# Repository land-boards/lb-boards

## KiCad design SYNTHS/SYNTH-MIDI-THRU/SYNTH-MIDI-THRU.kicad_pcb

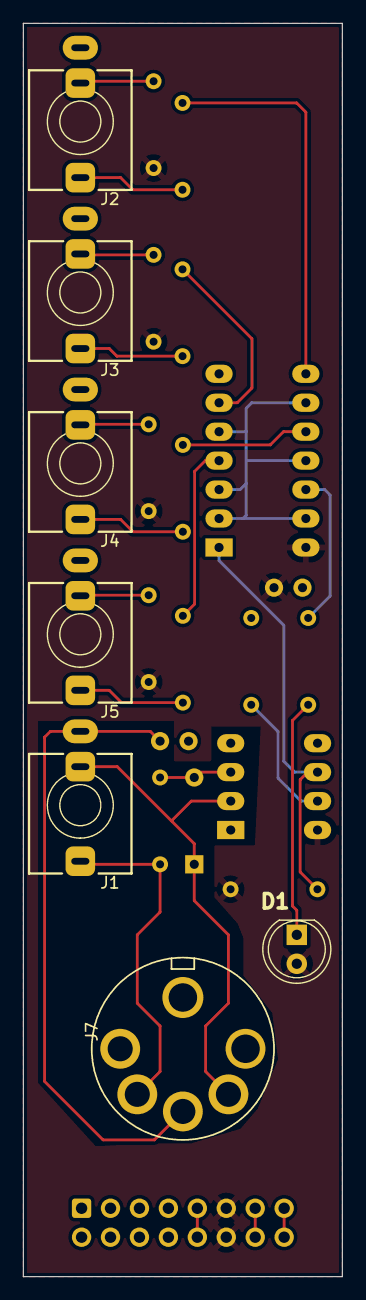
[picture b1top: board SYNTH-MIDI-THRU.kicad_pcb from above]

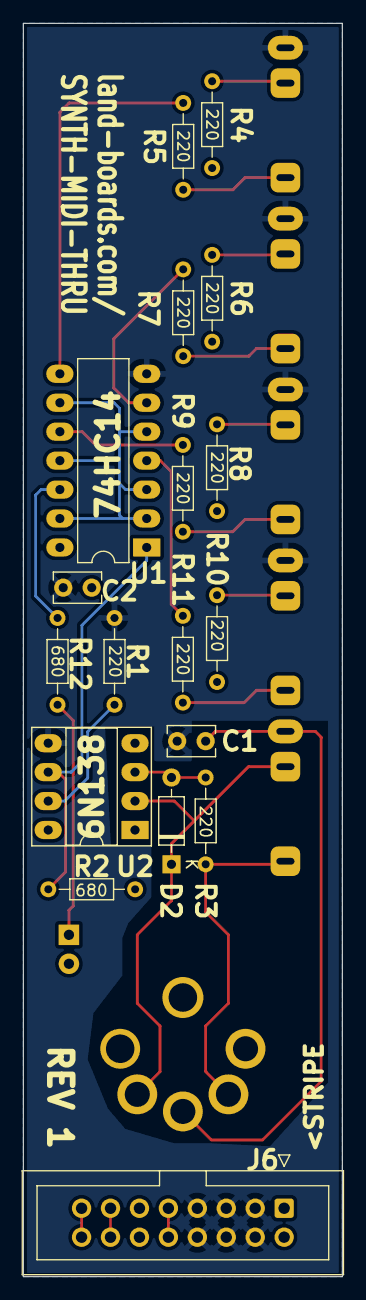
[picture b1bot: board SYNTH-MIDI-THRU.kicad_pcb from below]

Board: 2 copper layers, 28.0 x 110.0 mm, 25 parts (18 on the bottom side), 26 nets.

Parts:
C1, C2: 0.1uF; C_Rect_L4.0mm_W2.5mm_P2.50mm
D1: LED; LED_D5.0mm
D2: 1N914; D_DO-35_SOD27_P7.62mm_Horizontal
J1, J2, J3, J4, J5: AudioJack3; PJ-366ST
J6: Conn_02x08_Odd_Even; IDC-Header_2x08_P2.54mm_Vertical
J7: DIN-5; DIN-5_SD-50BV-Vertical
R1, R3, R4, R5, R6, R7, R8, R9, R10, R11: 220; R_Axial_DIN0204_L3.6mm_D1.6mm_P7.62mm_Horizontal
R2, R12: 680; R_Axial_DIN0204_L3.6mm_D1.6mm_P7.62mm_Horizontal
U1: 74HC14; DIP-14_W7.62mm_LongPads
U2: 6N138; DIP-8_W7.62mm_Socket_LongPads

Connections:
+5V: C2.1, D1.2 (A), J6.11, J6.12, R2.1, R4.1, R6.1, R8.1, R10.1, U1.14 (VCC), U2.8 (VCC)
+12V: J6.9, J6.10
/ALLRXD: U1.2, U1.3, U1.5, U1.9, U1.11, U1.13
/CV_OUT: J6.13, J6.14
/GATE_OUT: J6.15, J6.16
/MIDI_1_OUT: J2.T, R5.2
/MIDI_1_PWR: J2.R, R4.2
/MIDI_2_OUT: J3.T, R7.2
/MIDI_2_PWR: J3.R, R6.2
/MIDI_3_OUT: J4.T, R9.2
/MIDI_3_PWR: J4.R, R8.2
/MIDI_4_OUT: J5.T, R11.2
/MIDI_4_PWR: J5.R, R10.2
/MIDI_GND: C1.1, J1.S, J7.2
/MIDI_IN: D2.1 (K), J1.R, J7.4, U2.2 (C1)
/MIDI_RTN: J1.T, J7.5, R3.2
/RXD: R2.2, U1.1, U2.6 (VO2)
GND: C1.2, C2.2, J2.S, J3.S, J4.S, J5.S, J6.3, J6.4, J6.5, J6.6, J6.7, J6.8, R1.2, U1.7 (GND), U2.5 (GND)
unnamed: D1.1 (K), R12.2
unnamed: D2.2 (A), R3.1, U2.3 (C2)
unnamed: R1.1, U2.7 (VO1)
unnamed: R5.1, U1.8
unnamed: R7.1, U1.6
unnamed: R9.1, U1.10
unnamed: R11.1, U1.4
unnamed: R12.1, U1.12

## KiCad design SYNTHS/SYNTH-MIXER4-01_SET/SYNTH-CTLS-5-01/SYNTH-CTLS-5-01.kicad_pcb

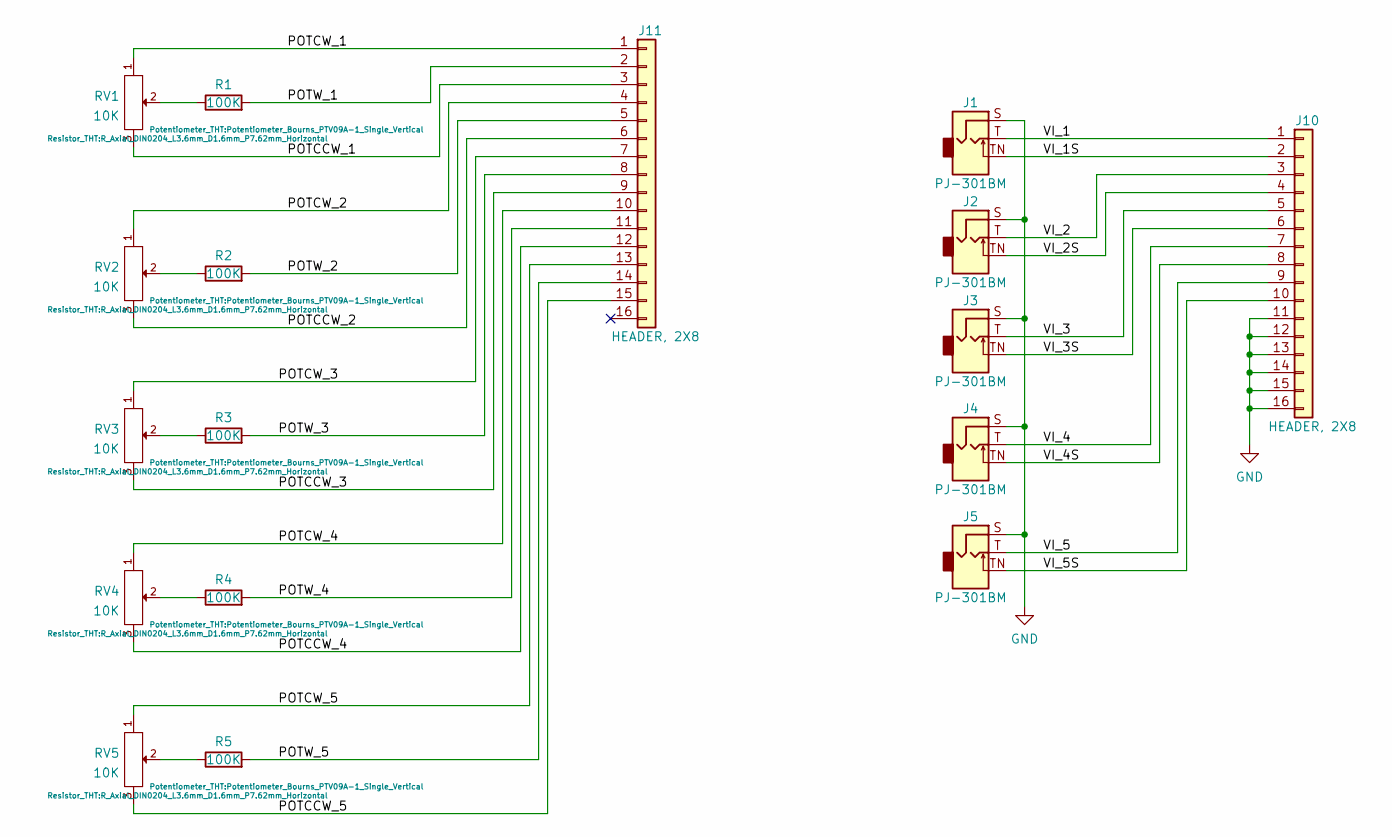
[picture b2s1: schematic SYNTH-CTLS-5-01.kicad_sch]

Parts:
J1, J2, J3, J4, J5: PJ-301BM; Jack_3.5mm_QingPu_WQP-PJ301BM_Vertical
J10, J11: HEADER, 2X8; PinHeader_2x08_P2.54mm_Vertical
R1, R2, R3, R4, R5: 100K; R_Axial_DIN0204_L3.6mm_D1.6mm_P7.62mm_Horizontal
RV1, RV2, RV3, RV4, RV5: 10K; Potentiometer_Bourns_PTV09A-1_Single_Vertical

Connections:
/POTCCW_1: J11.3, RV1.3
/POTCCW_2: J11.6, RV2.3
/POTCCW_3: J11.9, RV3.3
/POTCCW_4: J11.12, RV4.3
/POTCCW_5: J11.15, RV5.3
/POTCW_1: J11.1, RV1.1
/POTCW_2: J11.4, RV2.1
/POTCW_3: J11.7, RV3.1
/POTCW_4: J11.10, RV4.1
/POTCW_5: J11.13, RV5.1
/POTW_1: J11.2, R1.2
/POTW_2: J11.5, R2.2
/POTW_3: J11.8, R3.2
/POTW_4: J11.11, R4.2
/POTW_5: J11.14, R5.2
/VI_1: J1.T, J10.1
/VI_1S: J1.TN, J10.2
/VI_2: J2.T, J10.3
/VI_2S: J2.TN, J10.4
/VI_3: J3.T, J10.5
/VI_3S: J3.TN, J10.6
/VI_4: J4.T, J10.7
/VI_4S: J4.TN, J10.8
/VI_5: J5.T, J10.9
/VI_5S: J5.TN, J10.10
GND: J1.S, J2.S, J3.S, J4.S, J5.S, J10.11, J10.12, J10.13, J10.14, J10.15, J10.16
unnamed: R1.1, RV1.2
unnamed: R2.1, RV2.2
unnamed: R3.1, RV3.2
unnamed: R4.1, RV4.2
unnamed: R5.1, RV5.2

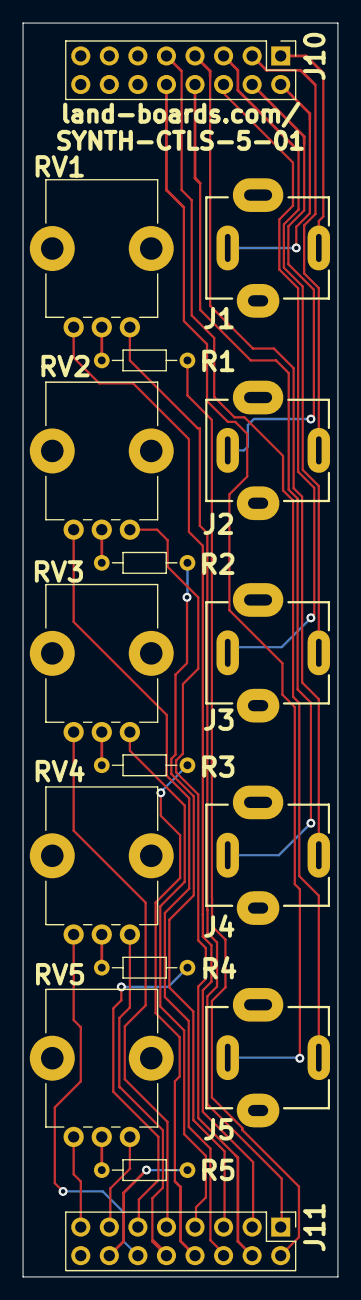
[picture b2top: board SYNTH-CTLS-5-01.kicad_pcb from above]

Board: 2 copper layers, 28.0 x 111.5 mm, 17 parts (0 on the bottom side), 31 nets.

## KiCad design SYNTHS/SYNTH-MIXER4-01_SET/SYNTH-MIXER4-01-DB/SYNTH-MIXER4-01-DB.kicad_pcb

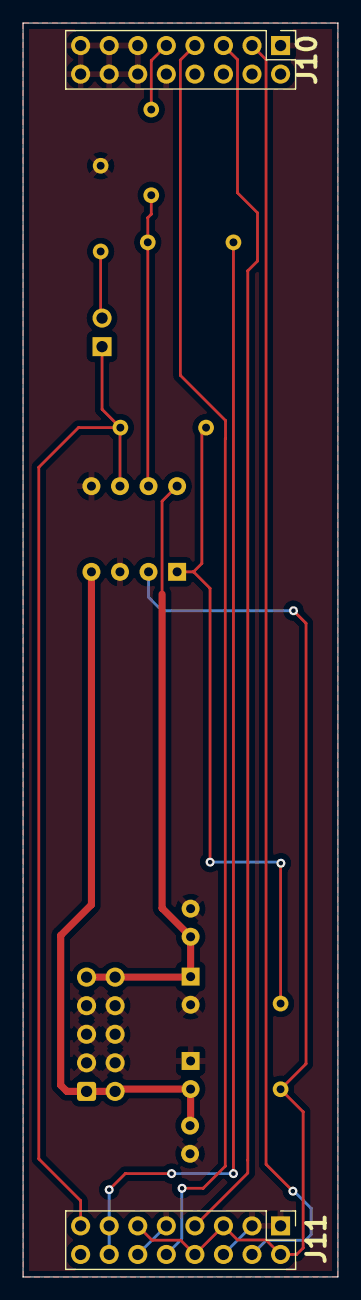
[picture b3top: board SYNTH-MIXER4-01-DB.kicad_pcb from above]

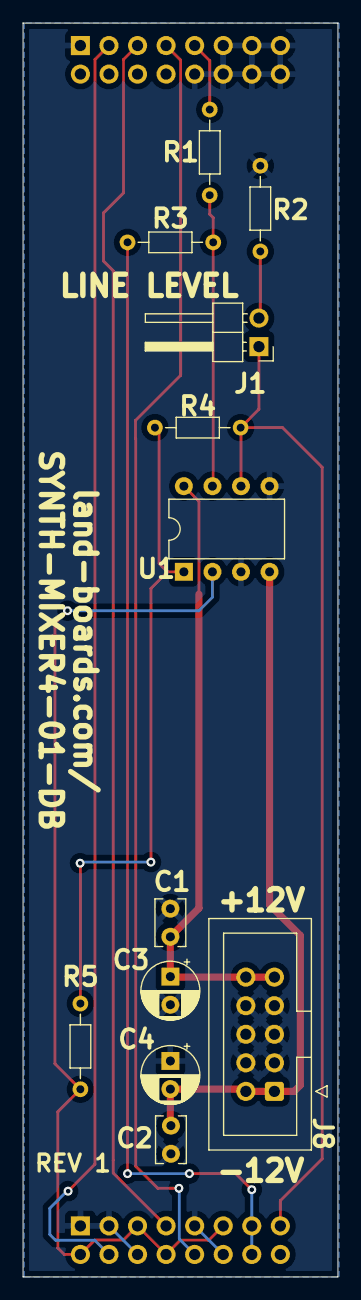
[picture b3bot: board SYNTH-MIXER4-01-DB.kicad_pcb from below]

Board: 2 copper layers, 28.0 x 111.5 mm, 14 parts (12 on the bottom side), 13 nets.

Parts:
C1, C2: 0.1uF; C_Rect_L4.0mm_W2.5mm_P2.50mm
C3, C4: 10uF; CP_Radial_D5.0mm_P2.50mm
J1: Conn_01x02; PinHeader_1x02_P2.54mm_Horizontal
J8: Conn_02x05; IDC-Header_2x05_P2.54mm_Vertical
J10, J11: HEADER, 2X8; PinHeader_2x08_P2.54mm_Vertical
R1: 1K; R_Axial_DIN0204_L3.6mm_D1.6mm_P7.62mm_Horizontal
R2, R4: 22K; R_Axial_DIN0204_L3.6mm_D1.6mm_P7.62mm_Horizontal
R3: 4.7K; R_Axial_DIN0204_L3.6mm_D1.6mm_P7.62mm_Horizontal
R5: 100K; R_Axial_DIN0204_L3.6mm_D1.6mm_P7.62mm_Horizontal
U1: TL072; DIP-8_W7.62mm

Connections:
+12V: C1.1, C3.1, J8.9, J8.10, U1.8 (V+)
-12V: C2.2, C4.2, J8.1, J8.2, U1.4 (V-)
/OUT: J10.9, R1.2
/VI_2: J10.3, J11.4
/VI_3: J10.5, J11.7
/VI_4: J10.7, J11.10
/VO: R1.1, R3.2, U1.7
/VOL1: J11.13, J11.14, R3.1
/VOL2: J1.1, J11.15, R4.2, U1.6 (-)
/VSUM: J11.2, J11.5, J11.8, J11.11, R5.1, U1.2 (-)
GND: C1.2, C2.1, C3.2, C4.1, J8.3, J8.4, J8.5, J8.6, J8.7, J8.8, J10.1, J10.10, J10.11, J10.12, J10.13, J10.14, J10.15, J10.16, J11.1, J11.3, J11.6, J11.9, J11.12, R2.1, U1.3 (+), U1.5 (+)
unnamed: J1.2, R2.2
unnamed: R4.1, R5.2, U1.1

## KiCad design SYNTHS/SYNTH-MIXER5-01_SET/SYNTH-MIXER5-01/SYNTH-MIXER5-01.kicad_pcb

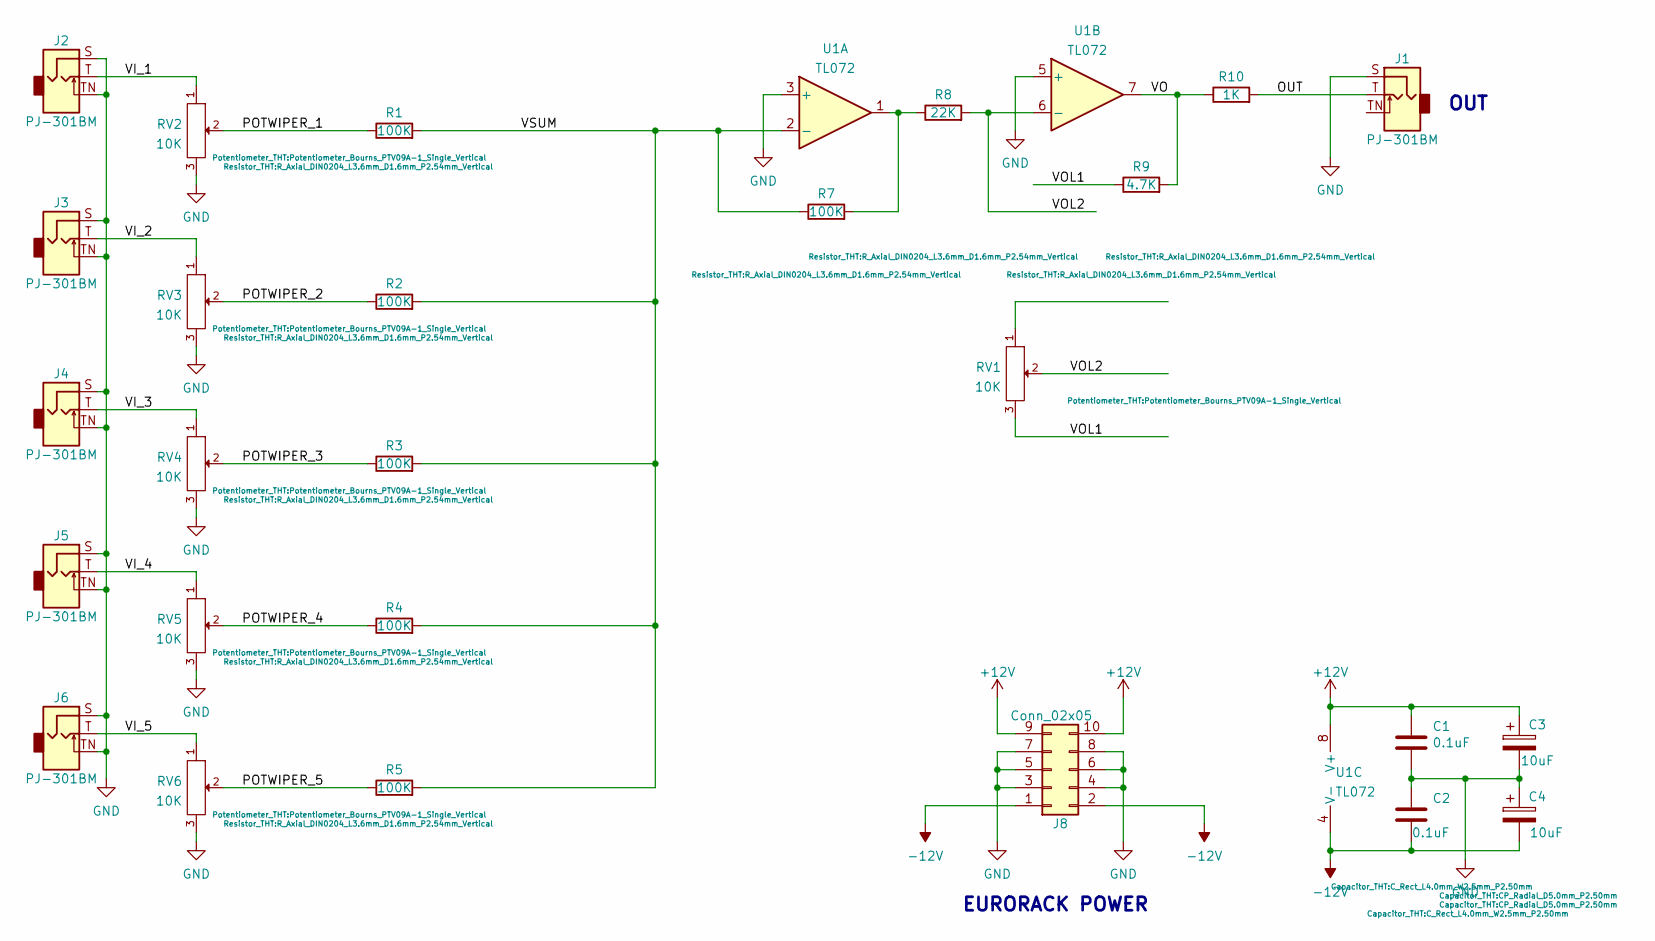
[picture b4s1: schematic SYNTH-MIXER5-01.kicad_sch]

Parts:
C1, C2: 0.1uF; C_Rect_L4.0mm_W2.5mm_P2.50mm
C3, C4: 10uF; CP_Radial_D5.0mm_P2.50mm
J1, J2, J3, J4, J5, J6: PJ-301BM; Jack_3.5mm_QingPu_WQP-PJ301BM_Vertical
J8: Conn_02x05; IDC-Header_2x05_P2.54mm_Vertical
R1, R2, R3, R4, R5, R7: 100K; R_Axial_DIN0204_L3.6mm_D1.6mm_P2.54mm_Vertical
R8: 22K; R_Axial_DIN0204_L3.6mm_D1.6mm_P2.54mm_Vertical
R9: 4.7K; R_Axial_DIN0204_L3.6mm_D1.6mm_P2.54mm_Vertical
R10: 1K; R_Axial_DIN0204_L3.6mm_D1.6mm_P2.54mm_Vertical
RV1, RV2, RV3, RV4, RV5, RV6: 10K; Potentiometer_Bourns_PTV09A-1_Single_Vertical
U1: TL072; DIP-8_W7.62mm

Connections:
+12V: C1.1, C3.1, J8.9, J8.10, U1.8 (V+)
-12V: C2.2, C4.2, J8.1, J8.2, U1.4 (V-)
/OUT: J1.T, R10.2
/POTWIPER_1: R1.1, RV2.2
/POTWIPER_2: R2.1, RV3.2
/POTWIPER_3: R3.1, RV4.2
/POTWIPER_4: R4.1, RV5.2
/POTWIPER_5: R5.1, RV6.2
/VI_1: J2.T, RV2.1
/VI_2: J3.T, RV3.1
/VI_3: J4.T, RV4.1
/VI_4: J5.T, RV5.1
/VI_5: J6.T, RV6.1
/VO: R9.2, R10.1, U1.7
/VOL1: R9.1, RV1.3
/VOL2: R8.2, RV1.2, U1.6 (-)
/VSUM: R1.2, R2.2, R3.2, R4.2, R5.2, R7.1, U1.2 (-)
GND: C1.2, C2.1, C3.2, C4.1, J1.S, J2.S, J2.TN, J3.S, J3.TN, J4.S, J4.TN, J5.S, J5.TN, J6.S, J6.TN, J8.3, J8.4, J8.5, J8.6, J8.7, J8.8, RV2.3, RV3.3, RV4.3, RV5.3, RV6.3, U1.3 (+), U1.5 (+)
unnamed: R7.2, R8.1, U1.1

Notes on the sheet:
EURORACK POWER
OUT

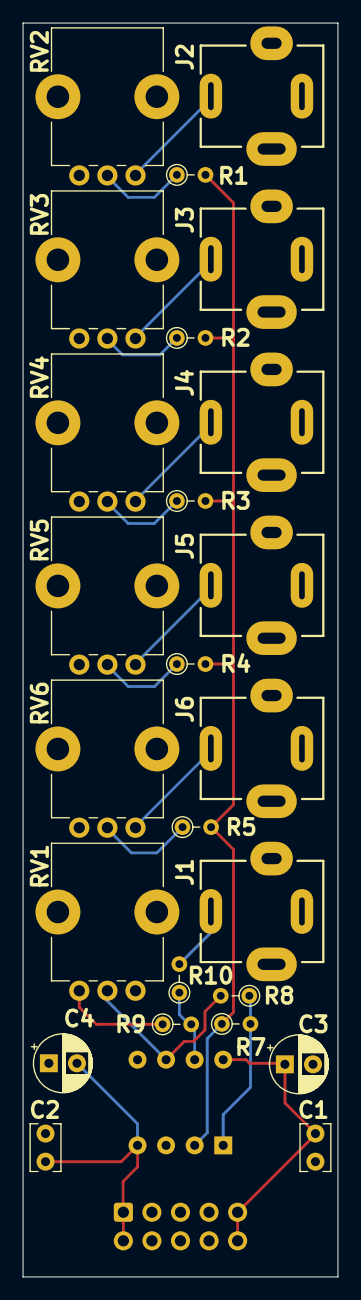
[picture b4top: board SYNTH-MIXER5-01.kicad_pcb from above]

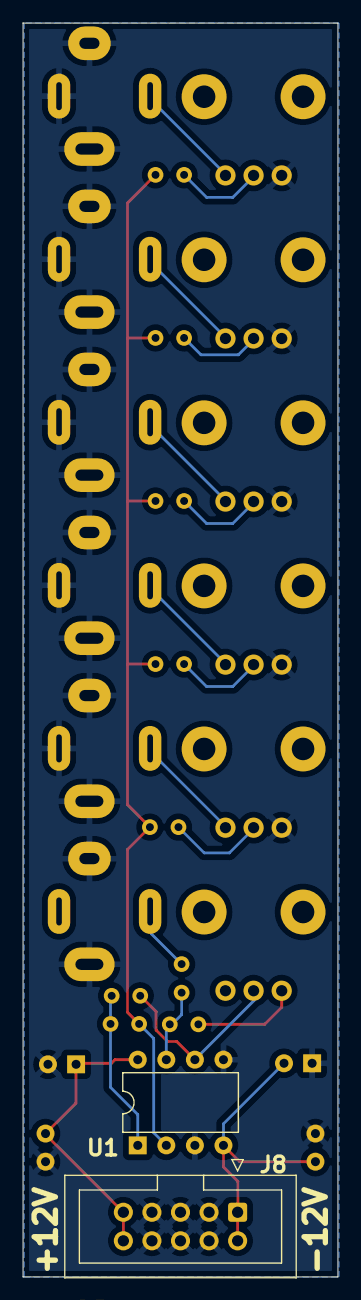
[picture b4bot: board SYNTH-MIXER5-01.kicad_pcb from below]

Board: 2 copper layers, 28.0 x 111.5 mm, 27 parts (2 on the bottom side), 19 nets.
